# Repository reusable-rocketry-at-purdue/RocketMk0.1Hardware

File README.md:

# RocketMk0.1Hardware
Eagle files for the first gimbal control system

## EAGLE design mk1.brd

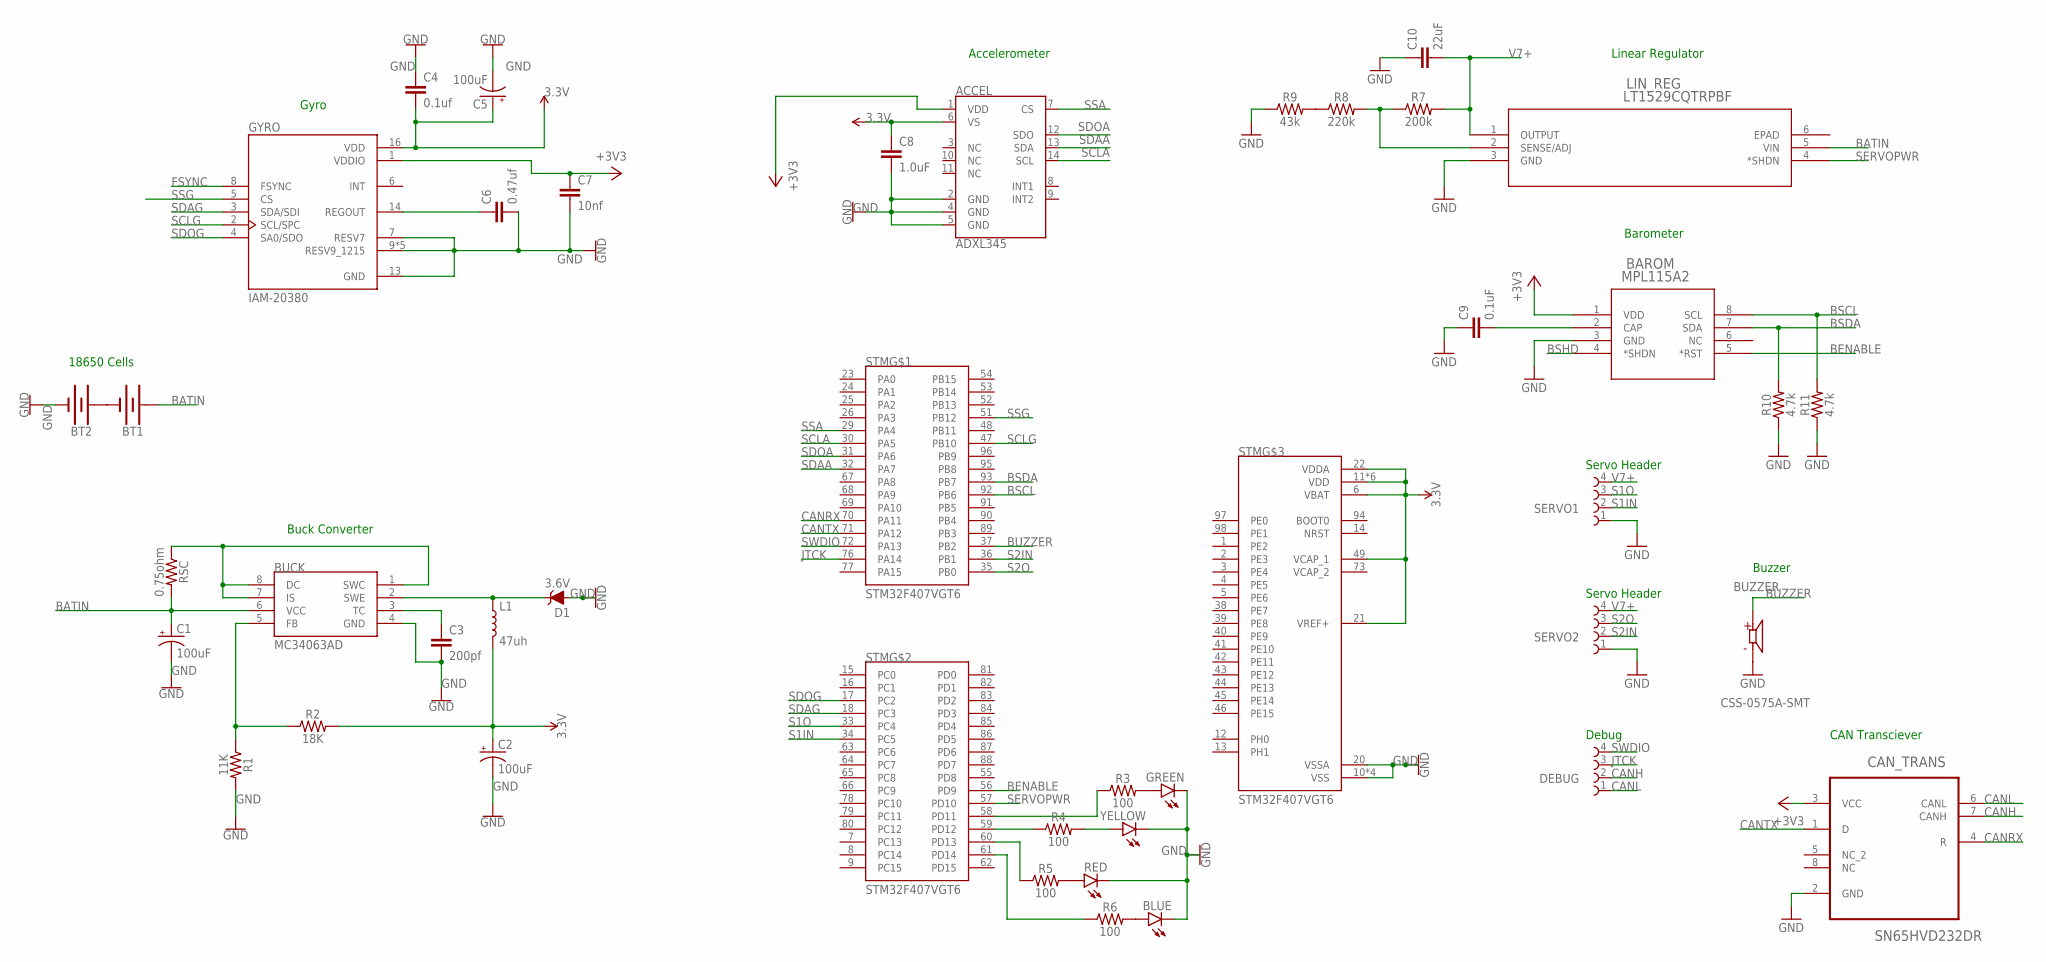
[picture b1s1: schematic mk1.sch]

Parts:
ACCEL: ADXL345; LGA-14
BAROM: MPL115A2; LGA8
BLUE: LEDSML0805; SML0805
BT1, BT2: BATTERY-18650; BATTERY_18650-HOLDER
BUCK: MC34063AD; SOIC8
BUZZER: CSS-0575A-SMT; CUI_CSS-0575A-SMT
C1, C2, C5: 100uF; 1206-POLAR
C3: 200pf; 0805
C4: 0.1uf; 0805
C6: 0.47uf; 0805
C7: 10nf; 0805
C8: 1.0uF; 0805
C9: 0.1uF; 0603
C10: 22uF; 0805
CAN_TRANS: SN65HVD232DR; SOIC127P600X175-8N
D1: 3.6V; SOD-323
DEBUG: 61300411121
GREEN: LEDSML0805; SML0805
GYRO: IAM-20380; PQFN50P300X300X80-16N
L1: 47uh; 0805
LIN_REG: LT1529CQTRPBF; DDPAK-5_Q
R1: 11K; 0805
R2: 18K; 0805
R3, R4, R5, R6: 100; 0805
R7: 200k; 0603
R8: 220k; 0603
R9: 43k; 0603
R10, R11: 4.7k; 0603
RED: LEDSML0805; SML0805
RSC: 0.75ohm; 0805
SERVO1, SERVO2: 61300411121
STM: STM32F407VGT6; QFP50P1600X1600X160-100N
YELLOW: LEDSML0805; SML0805

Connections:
3.3V: ACCEL.6 (VS), C2.1 (+), C4.2, C5.1 (+), C8.1, GYRO.16 (VDD), L1.2, R2.2, STM.6 (VBAT), STM.11 (VDD), STM.19 (VDD), STM.21 (VREF+), STM.22 (VDDA), STM.28 (VDD), STM.49 (VCAP_1), STM.50 (VDD), STM.75 (VDD), STM.100 (VDD)
+3V3: ACCEL.1 (VDD), BAROM.1 (VDD), C7.1, CAN_TRANS.3 (VCC), GYRO.1 (VDDIO)
BATIN: BT1.PWR@1 (+), BUCK.6 (VCC), C1.1 (+), LIN_REG.5 (VIN), RSC.2
BATIN1: BT1.GND@1 (-), BT2.PWR@1 (+)
BENABLE: BAROM.5 (*RST), STM.56 (PD9)
BSCL: BAROM.8 (SCL), R11.2, STM.92 (PB6)
BSDA: BAROM.7 (SDA), R10.2, STM.93 (PB7)
BSHD: BAROM.4 (*SHDN)
BUZZER: BUZZER.1, STM.37 (PB2)
CANH: CAN_TRANS.7 (CANH), DEBUG.2
CANL: CAN_TRANS.6 (CANL), DEBUG.1
CANRX: CAN_TRANS.4 (R), STM.70 (PA11)
CANTX: CAN_TRANS.1 (D), STM.71 (PA12)
FSYNC: GYRO.8 (FSYNC)
GND: ACCEL.2 (GND), ACCEL.4 (GND), ACCEL.5 (GND), BAROM.3 (GND), BLUE.C, BT2.GND@1 (-), BUCK.4 (GND), BUZZER.2 (N), C1.2 (-), C2.2 (-), C3.2, C4.1, C5.2 (-), C6.2, C7.2, C8.2, C9.1, C10.1, CAN_TRANS.2 (GND), D1.A, GREEN.C, GYRO.7 (RESV7), GYRO.9 (RESV9_1215), GYRO.10 (RESV9_1215), GYRO.11 (RESV9_1215), GYRO.12 (RESV9_1215), GYRO.13 (GND), GYRO.15 (RESV9_1215), LIN_REG.3 (GND), R1.2, R9.1, R10.1, R11.1, RED.C, SERVO1.1, SERVO2.1, STM.10 (VSS), STM.20 (VSSA), STM.27 (VSS), STM.74 (VSS), STM.99 (VSS), YELLOW.C
JTCK: DEBUG.3, STM.76 (PA14)
unnamed: BUCK.1 (SWC), BUCK.7 (IS), BUCK.8 (DC), RSC.1
unnamed: BUCK.5 (FB), R1.1, R2.1
unnamed: BUCK.3 (TC), C3.1
unnamed: C6.1, GYRO.14 (REGOUT)
unnamed: BUCK.2 (SWE), D1.C, L1.1
unnamed: GREEN.A, R3.2
unnamed: R4.2, YELLOW.A
unnamed: R5.2, RED.A
unnamed: BLUE.A, R6.2
unnamed: R3.1, STM.58 (PD11)
unnamed: R4.1, STM.59 (PD12)
unnamed: R5.1, STM.60 (PD13)
unnamed: R6.1, STM.61 (PD14)
unnamed: LIN_REG.2 (SENSE/ADJ), R7.1, R8.2
unnamed: R8.1, R9.2
unnamed: BAROM.2 (CAP), C9.2
S1IN: SERVO1.2, STM.34 (PC5)
S1O: SERVO1.3, STM.33 (PC4)
S2IN: SERVO2.2, STM.36 (PB1)
S2O: SERVO2.3, STM.35 (PB0)
SCLA: ACCEL.14 (SCL), STM.30 (PA5)
SCLG: GYRO.2 (SCL/SPC), STM.47 (PB10)
SDAA: ACCEL.13 (SDA), STM.32 (PA7)
SDAG: GYRO.3 (SDA/SDI), STM.18 (PC3)
SDOA: ACCEL.12 (SDO), STM.31 (PA6)
SDOG: GYRO.4 (SA0/SDO), STM.17 (PC2)
SERVOPWR: LIN_REG.4 (*SHDN), STM.57 (PD10)
SSA: ACCEL.7 (CS), STM.29 (PA4)
SSG: GYRO.5 (CS), STM.51 (PB12)
SWDIO: DEBUG.4, STM.72 (PA13)
V7+: C10.2, LIN_REG.1 (OUTPUT), R7.2, SERVO1.4, SERVO2.4

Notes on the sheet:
Barometer
Linear Regulator
Buck Converter
18650 Cells
Gyro
Accelerometer
Servo Header
Debug
Buzzer
CAN Transciever

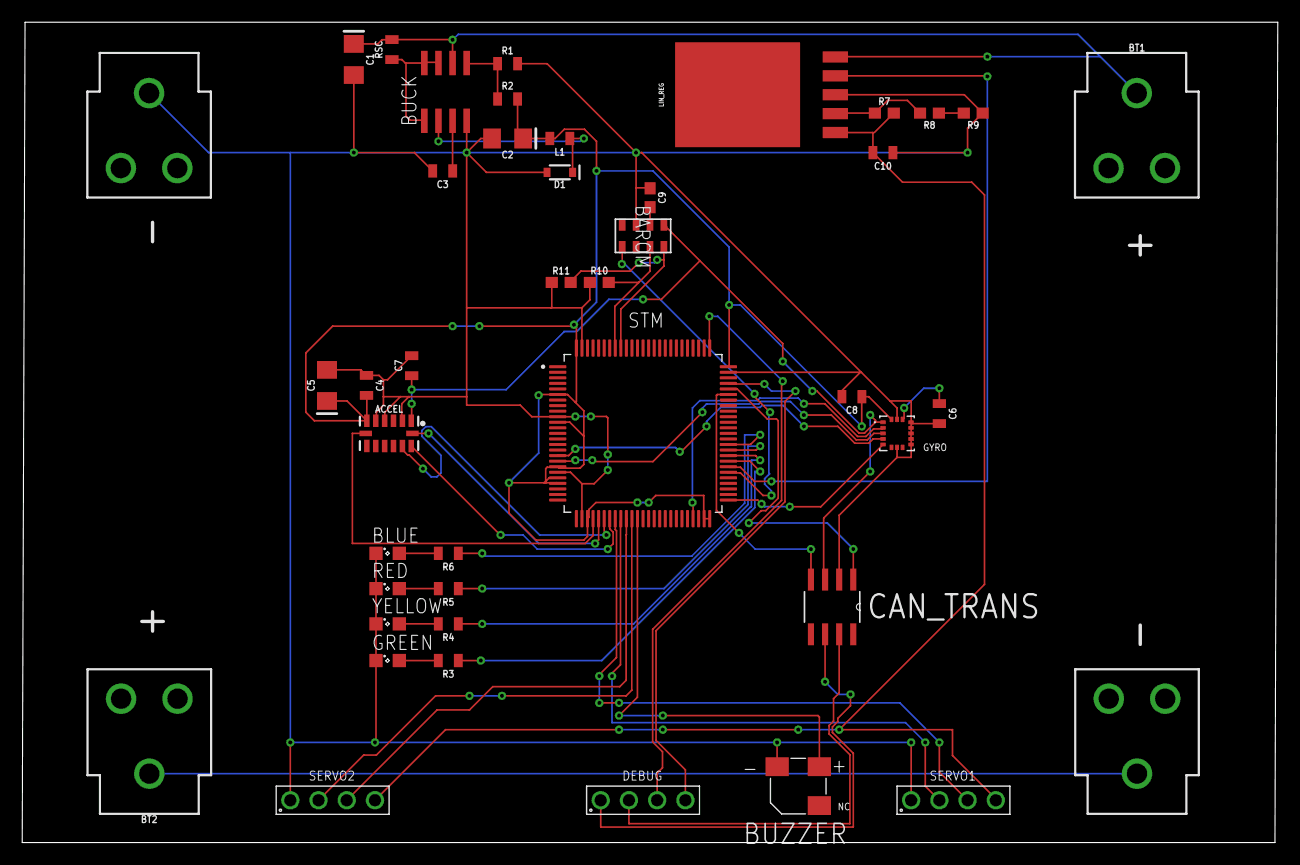
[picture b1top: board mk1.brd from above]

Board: 2 copper layers, 113.0 x 73.8 mm, 41 parts (0 on the bottom side), 45 nets.

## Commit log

2019-09-29 Create gitignore with MacOS desktop files excluded
2019-10-19 Created schematic and board for rocket
2019-10-19 Changed values of passive components around mc3406
2019-10-22 Update Rev 1 with reroute
2019-10-22 Added silkscreen names/logo
2019-10-22 LTspice file for buck
2019-11-16 Init for rev2
2019-11-17 Initial schematic layouts
2019-11-23 Added components and second board

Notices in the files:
parts and their libraries:
SparkFun-Batteries: Licensing: Creative Commons ShareAlike 4.0 International - https://creativecommons.org/licenses/by-sa/4.0
Wurth_Elektronik_Electromechanic_Board_t: Copyright: Würth Elektronik
